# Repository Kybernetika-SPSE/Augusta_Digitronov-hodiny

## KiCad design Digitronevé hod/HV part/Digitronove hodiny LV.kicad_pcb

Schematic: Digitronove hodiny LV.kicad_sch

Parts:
C1, C9: 100 uF; CP_Radial_D6.3mm_P2.50mm
C2, C3, C4, C5, C6, C7: 100 nF; C_1206_3216Metric_Pad1.33x1.80mm_HandSolder
C8: 4.7 µF; CP_Radial_D10.0mm_P5.00mm
H1, H2, H3: MountingHole; MountingHole_2.5mm
J1: Conn_01x02; JST_EH_B2B-EH-A_1x02_P2.50mm_Vertical
J2: Conn_01x09; JST_EH_B9B-EH-A_1x09_P2.50mm_Vertical
NE1, NE2: Lamp_Neon; C_Rect_L4.0mm_W2.5mm_P2.50mm
Q1: MPSA42; TO-92_Inline
R1: 100K; R_Axial_DIN0207_L6.3mm_D2.5mm_P10.16mm_Horizontal
R2, R3, R4, R5: 10k; R_Axial_DIN0207_L6.3mm_D2.5mm_P10.16mm_Horizontal
R6, R7: 180k; R_Axial_DIN0207_L6.3mm_D2.5mm_P10.16mm_Horizontal
R8: 1M; R_Axial_DIN0207_L6.3mm_D2.5mm_P10.16mm_Horizontal
R9: 1k; R_Axial_DIN0207_L6.3mm_D2.5mm_P10.16mm_Horizontal
U1, U2: 74HC595; 74HC595N
U3, U4, U5, U6: K155id1; 74141
U7, U8, U9, U10: Tesla_ZM1082

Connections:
/0a: U6.16 (Q0), U10.11 (k9)
/0b: U5.16 (Q0), U9.11 (k9)
/0c: U4.16 (Q0), U8.11 (k9)
/0d: U3.16 (Q0), U7.11 (k9)
/1a: U6.15 (Q1), U10.9 (k8)
/1b: U5.15 (Q1), U9.9 (k8)
/1c: U4.15 (Q1), U8.9 (k8)
/1d: U3.15 (Q1), U7.9 (k8)
/2a: U6.8 (Q2), U10.8 (k7)
/2b: U5.8 (Q2), U9.8 (k7)
/2c: U4.8 (Q2), U8.8 (k7)
/2d: U3.8 (Q2), U7.8 (k7)
/3a: U6.9 (Q3), U10.7 (k6)
/3b: U5.9 (Q3), U9.7 (k6)
/3c: U4.9 (Q3), U8.7 (k6)
/3d: U3.9 (Q3), U7.7 (k6)
/4a: U6.13 (Q4), U10.6 (k5)
/4b: U5.13 (Q4), U9.6 (k5)
/4c: U4.13 (Q4), U8.6 (k5)
/4d: U3.13 (Q4), U7.6 (k5)
/5a: U6.14 (Q5), U10.5 (k4)
/5b: U5.14 (Q5), U9.5 (k4)
/5c: U4.14 (Q5), U8.5 (k4)
/5d: U3.14 (Q5), U7.5 (k4)
/6a: U6.11 (Q6), U10.3 (k3)
/6b: U5.11 (Q6), U9.3 (k3)
/6c: U4.11 (Q6), U8.3 (k3)
/6d: U3.11 (Q6), U7.3 (k3)
/7a: U6.10 (Q7), U10.2 (k2)
/7b: U5.10 (Q7), U9.2 (k2)
/7c: U4.10 (Q7), U8.2 (k2)
/7d: U3.10 (Q7), U7.2 (k2)
/8a: U6.1 (Q8), U10.1 (k1)
/8b: U5.1 (Q8), U9.1 (k1)
/8c: U4.1 (Q8), U8.1 (k1)
/8d: U3.1 (Q8), U7.1 (k1)
/9a: U6.2 (Q9), U10.12 (k0)
/9b: U5.2 (Q9), U9.12 (k0)
/9c: U4.2 (Q9), U8.12 (k0)
/9d: U3.2 (Q9), U7.12 (k0)
/+3V3: C1.1, C1.2, C2.2, C3.2, J2.3, U1.10 (~SRCLR), U1.16 (VCC), U2.10 (~SRCLR), U2.16 (VCC)
/+170V: C8.1, J1.2, NE1.1, NE1.2, NE2.1, NE2.2, Q1.1 (E), R2.1, R2.2, R3.1, R3.2, R4.1, R4.2, R5.1, R5.2, R6.1, R6.2, R7.1, R7.2, R8.2, R9.1, R9.2, U7.13 (a), U8.13 (a), U9.13 (a), U10.13 (a)
/A1: U2.15 (QA), U6.3 (A)
/A2: U2.4 (QE), U5.3 (A)
/A3: U1.15 (QA), U4.3 (A)
/A4: U1.4 (QE), U3.3 (A)
/B1: U2.1 (QB), U6.6 (B)
/B2: U2.5 (QF), U5.6 (B)
/B3: U1.1 (QB), U4.6 (B)
/B4: U1.5 (QF), U3.6 (B)
/C1: U2.2 (QC), U6.7 (C)
/C2: U2.6 (QG), U5.7 (C)
/C3: U1.2 (QC), U4.7 (C)
/C4: U1.6 (QG), U3.7 (C)
/D1: U2.3 (QD), U6.4 (D)
/D2: U2.7 (QH), U5.4 (D)
/D3: U1.3 (QD), U4.4 (D)
/D4: U1.7 (QH), U3.4 (D)
/NE1,2: J2.1, Q1.2 (B), R1.1
/OE: J2.8, U1.13 (~OE), U2.13 (~OE)
/RLCK: J2.7, U1.12 (RCLK), U2.12 (RCLK)
/SER1: J2.9, U2.14 (SER)
/SER2: U1.14 (SER), U2.9 (QH')
/SRLCK: J2.6, U1.11 (SRCLK), U2.11 (SRCLK)
GND: C2.1, C3.1, C4.2, C5.2, C6.2, C7.2, C8.2, J1.1, J2.4, J2.5, Q1.3 (C), R1.2, R8.1, U1.8 (GND), U2.8 (GND), U3.12 (GND), U4.12 (GND), U5.12 (GND), U6.12 (GND)

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
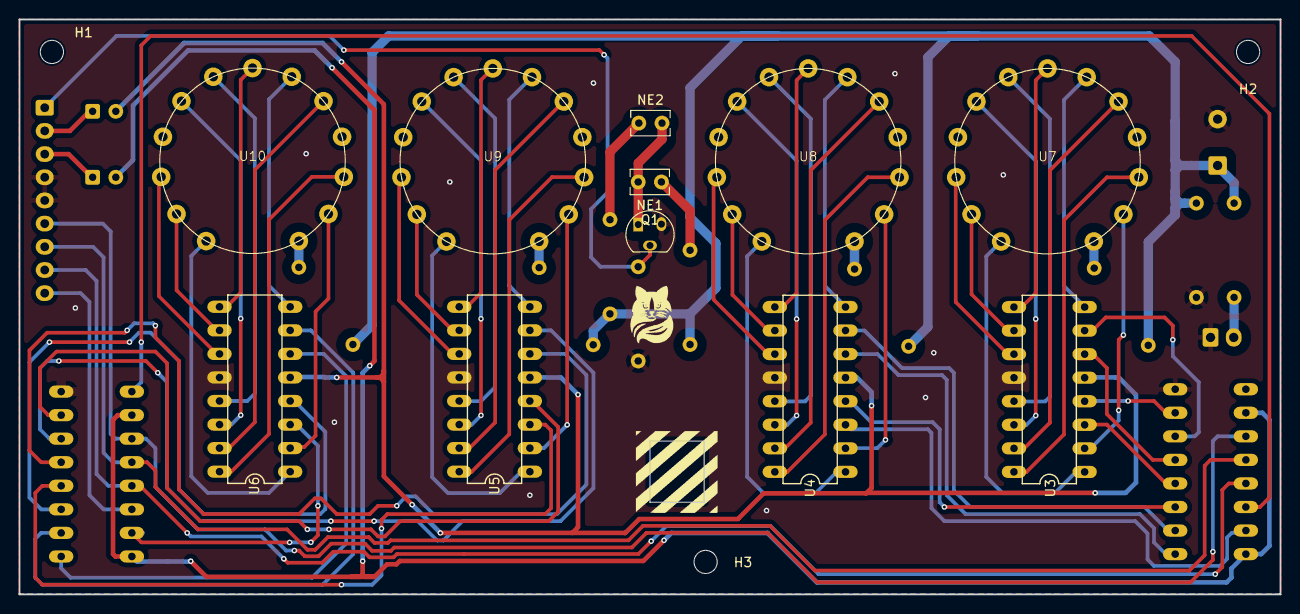
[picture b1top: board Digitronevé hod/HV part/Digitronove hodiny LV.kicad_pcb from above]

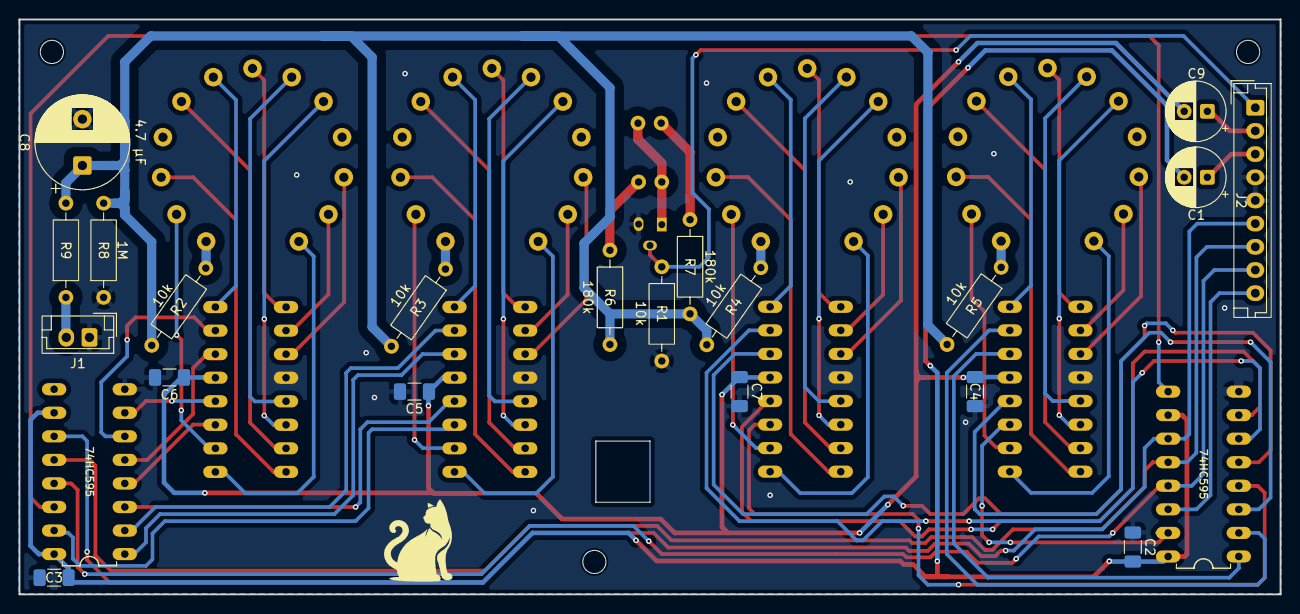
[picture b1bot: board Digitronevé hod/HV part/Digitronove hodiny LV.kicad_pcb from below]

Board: 2 copper layers, 136.0 x 62.0 mm, 36 parts (22 on the bottom side), 66 nets.

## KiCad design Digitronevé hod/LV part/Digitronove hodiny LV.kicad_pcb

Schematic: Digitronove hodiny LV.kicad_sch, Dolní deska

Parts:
C1: 100uF; CP_Radial_D6.3mm_P2.50mm
C2, C3, C4: 100nF; C_1206_3216Metric_Pad1.33x1.80mm_HandSolder
D1: 1N5817; D_DO-41_SOD81_P10.16mm_Horizontal
DS1: Conn_01x06; DS3231
F1, F2: Fuse; Fuse_1812_4532Metric
H1, H2, H3: MountingHole; MountingHole_2.5mm
J1: PDC004-PD
J2: MAX1771
J4: GY-VL53L0X
Konektor1: Conn_01x09; JST_EH_B9B-EH-A_1x09_P2.50mm_Vertical
Q1: NPN
R1, R3: 10k; R_1206_3216Metric_Pad1.30x1.75mm_HandSolder
R2, R4, R5, R6, R7, R8, R9, R10, R11: 4.7k; R_1206_3216Metric_Pad1.30x1.75mm_HandSolder
SW1: START/STOP; SW_PUSH_6mm_H4.3mm
SW2: EN; SW_PUSH_6mm_H4.3mm
SW3: +1; SW_PUSH_6mm_H4.3mm
SW4: SWITCH; SW_PUSH_6mm_H4.3mm
U1: DD4012SA; Untitled_3
U2: ESP32 DevKit; MODULE_ESP32_DEVKIT_V1; PARTREV N/A

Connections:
/+1: C3.2, R10.2, U2.21 (D32)
/+3V3: DS1.+3V3, J4.+3V3, Konektor1.3, R1.1, R2.1, R4.2, R6.1, R6.2, R7.1, R8.1, R8.2, R9.1, R9.2, R10.1, R11.1, SW1.2, SW3.2, SW4.2, U2.1 (3V3)
/+5V: C1.1, D1.1 (K), D1.2 (A), Konektor1.2, U1.3 (OUT), U2.30 (VIN)
/+9V: F1.1, F1.2, F2.1, F2.2, J1.1, J2.VIN (Pin_1), U1.1 (IN)
/EN: SW2.2, U2.16 (EN)
/NE1,2: Konektor1.1, R5.1, R5.2, U2.4 (D2)
/OE: Konektor1.8, U2.14 (D22)
/RLCK: Konektor1.7, U2.23 (D25)
/SCL: DS1.SCL, J4.SCL, R2.2, U2.5 (D4)
/SDA: DS1.SDA, J4.SDA, R4.1, U2.9 (D18)
/SER1: Konektor1.9, U2.25 (D27)
/SHDN: J2.SHDN (Pin_3), Q1.1 (C), Q1.2 (B), R3.1, R3.2, U2.28 (D13)
/SQW: DS1.SQW, R1.2, U2.20 (D35)
/SRLCK: Konektor1.6, U2.24 (D26)
/START-STOP: C2.2, R7.2, U2.15 (D23)
/SWITCH: C4.2, R11.2, U2.22 (D33)
GND: C1.2, C2.1, C3.1, C4.1, DS1.GND, J1.2, J2.GND (Pin_2), J4.GND, Konektor1.4, Konektor1.5, Q1.3 (E), SW1.1, SW2.1, SW3.1, SW4.1, U1.2 (GND), U2.2 (GND), U2.29 (GND)

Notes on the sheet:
USB-C s modulem Ip2721

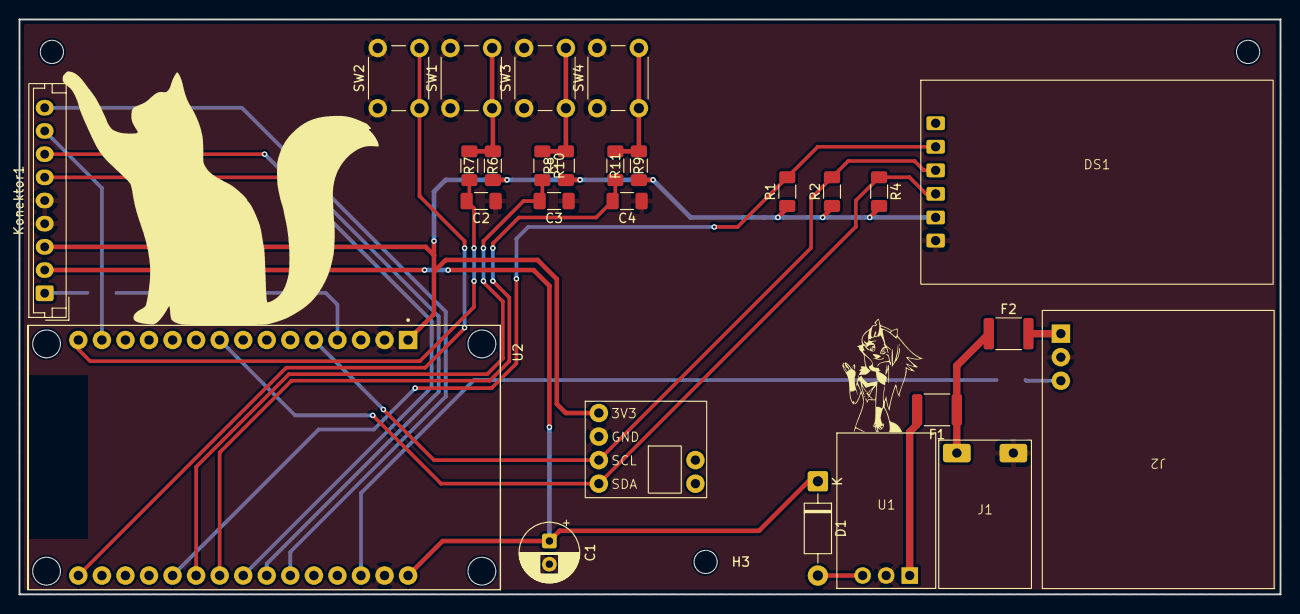
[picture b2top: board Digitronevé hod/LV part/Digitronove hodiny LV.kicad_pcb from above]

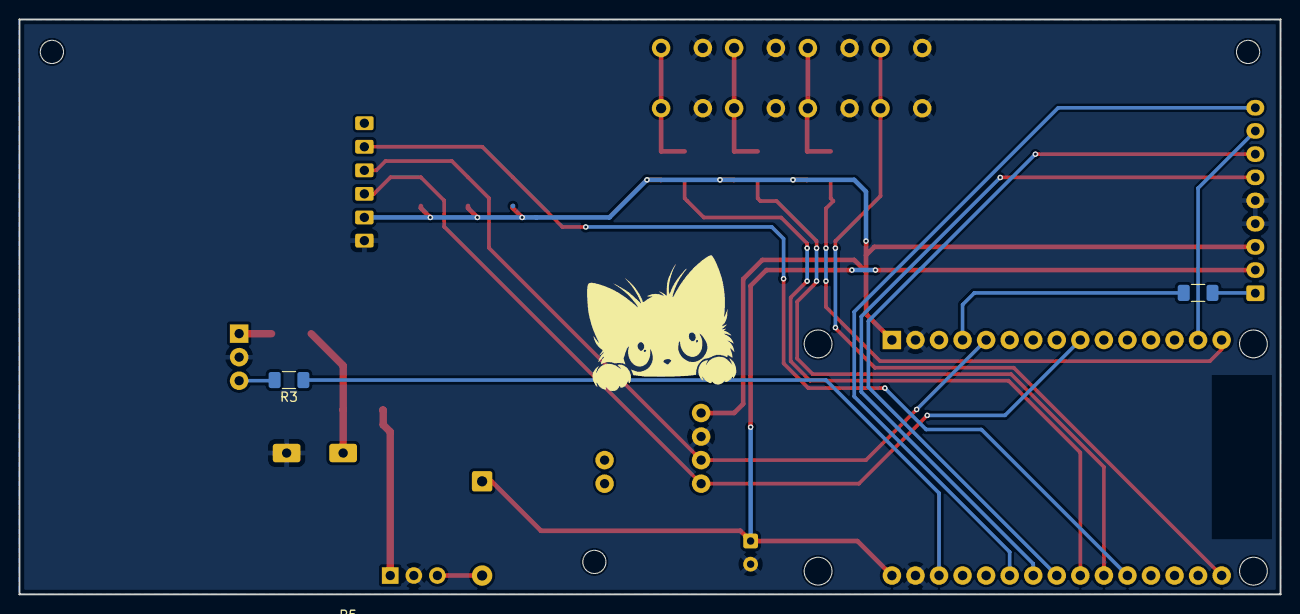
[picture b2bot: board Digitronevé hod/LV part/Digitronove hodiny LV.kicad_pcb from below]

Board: 2 copper layers, 136.0 x 62.0 mm, 32 parts (2 on the bottom side), 17 nets.

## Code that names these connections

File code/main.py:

from machine import Pin, I2C
import time


led = Pin(2, Pin.OUT)


for i in range(1):
    led.value(1)       
    time.sleep(0.2)    
    led.value(0)       
    time.sleep(0.2)    

try:
    import ds3231
    import vl53l0x
    i2c_available = True
except ImportError:
    i2c_available = False

# --- NASTAVENI PINU PODLE SCHEMATU ---
btn_start_stop = Pin(23, Pin.IN) 
btn_plus_one   = Pin(32, Pin.IN) 
btn_switch     = Pin(33, Pin.IN) 

# Posuvne registry 74HC595
pin_ser   = Pin(27, Pin.OUT) 
pin_srclk = Pin(26, Pin.OUT) 
pin_rlck  = Pin(25, Pin.OUT) 
pin_oe    = Pin(22, Pin.OUT)  

# Bezpecne vychozi stavy pro 74HC595 (zadne nahodne pulzy pri startu)
pin_ser.value(0)
pin_srclk.value(0)
pin_rlck.value(0)
pin_oe.value(0)

# NOVE PINY: Menic a Tecky
pin_shdn  = Pin(13, Pin.OUT) # SHDN - Zapinani 170V menice (IO14)
pin_dots  = Pin(2, Pin.OUT)  # D2 - Zapinani tecek mezi cislicemi (GPIO 2)

# --- INICIALIZACE I2C a SENZORU ---
i2c = I2C(0, scl=Pin(4), sda=Pin(18), freq=400000)

if i2c_available:
    rtc = ds3231.DS3231(i2c)
    sensor = vl53l0x.VL53L0X(i2c) # Tady ho rovnou pojmenujeme sensor

# --- GLORBO FLORBO
current_hour = 00
current_minute = 00
display_on = False
frozen_time = False
freeze_start_time = 0
set_mode = 0 # 0 = Bezny provoz, 1 = Nastaveni HODIN, 2 = Nastaveni MINUT
posledni_pohyb_cas = time.ticks_ms() 

# --- Fce ---
def turn_on_display():
    global display_on
    pin_oe.value(0)   
    pin_shdn.value(1) 
    display_on = True

def turn_off_display():
    global display_on
    pin_shdn.value(0) 
    pin_oe.value(1)  
    pin_dots.value(0) 
    display_on = False

def dec_to_bcd(val):
    """Prevede klasicke cislo (napr. 34) na BCD format pro K155ID1"""
    tens = val // 10
    units = val % 10
    return (tens << 4) | units

def update_shift_registers(hours, minutes):
    bcd_hours = dec_to_bcd(hours)
    bcd_minutes = dec_to_bcd(minutes)
    
    # hod:min
    data_to_send = (bcd_hours << 8) | bcd_minutes

    # Pri shiftovani docasne vypneme vystup, aby nevznikaly artefakty.
    output_was_enabled = (pin_oe.value() == 0)
    if output_was_enabled:
        pin_oe.value(1)
    
    pin_rlck.value(0)
    for i in range(15, -1, -1):
        bit = (data_to_send >> i) & 1
        pin_ser.value(bit)

        pin_srclk.value(1)
        pin_srclk.value(0)
        
    pin_rlck.value(1)
    pin_rlck.value(0)

    if output_was_enabled:
        pin_oe.value(0)
    
    

    # --- HLAVNI SMYCAK  ---
while True:
    now = time.ticks_ms()
    
    if i2c_available:
        try:
            distance = sensor.read() 
            if distance >= 150 and distance <= 300:
                posledni_pohyb_cas = now 
                if not display_on:
                    turn_on_display()
        except:
            pass 
            
    # === CTENI REALNEHO CASU Z RTC ===
    if i2c_available and set_mode == 0 and not frozen_time:
        try:
            cas = rtc.datetime() 
        
            current_hour = cas[4]   
            current_minute = cas[5] 
        except:
            pass
            
    # 2. ZHASINANI DIGITRONEK
    if display_on and set_mode == 0:
        if time.ticks_diff(now, posledni_pohyb_cas) > 8000:
            turn_off_display()

    # 3. DOTS
    if display_on:
        if set_mode == 0:
            if (now % 2000) < 1000:
                pin_dots.value(1)
            else:
                pin_dots.value(0)
        else:
            pin_dots.value(1)
    
    # 4. Zmrazeni casu 
    if btn_start_stop.value() == 0:
        if not frozen_time:
            frozen_time = True
            freeze_start_time = now
        time.sleep(0.3)
            
    if frozen_time and time.ticks_diff(now, freeze_start_time) > 10000:
        frozen_time = False

    # 5. Prepinani rezimu nastaveni (Switch) a ULOZENI CASU
    if btn_switch.value() == 0:
        stary_rezim = set_mode
        set_mode = (set_mode + 1) % 3
        

        if stary_rezim != 0 and set_mode == 0 and i2c_available:
            try:
                novy_cas = (2025, 1, 1, current_hour, current_minute, 0, 0)
                rtc.datetime(novy_cas)
                
            except:
                pass

        posledni_pohyb_cas = now
        if not display_on: turn_on_display()
        time.sleep(0.3)

    # 6. Pridavani casu (+1)
    if btn_plus_one.value() == 0:
        if set_mode == 1:
            current_hour = (current_hour + 1) % 24
        elif set_mode == 2:
            current_minute = (current_minute + 1) % 60
        posledni_pohyb_cas = now 
        if not display_on: turn_on_display()
        time.sleep(0.2) 

    # 7. Zobrazeni 
    if display_on:
        # Pri aktivnim zobrazeni drz drivery trvale zapnute.
        pin_shdn.value(1)
        pin_oe.value(0)
        update_shift_registers(current_hour, current_minute)
    
    time.sleep(0.05)

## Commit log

2025-10-30 Fix project name formatting in README
2025-12-21 PCB 21.12.2025
2025-12-22 Dodání pouzder
2025-12-22 Dodávní pouzder part2
2025-12-22 LV Schema
2025-12-26 schéma LV desky update
2025-12-26 PCB LV upravování pouzder
2025-12-28 Update Schéma LV
2025-12-28 Dokončení LV
2025-12-30 HV part schematic 01
2026-01-03 HV scheme update
2026-01-06 LV update
2026-02-05 Redesign LV
2026-02-16 Před kontrolou
2026-02-21 PCB finnal
2026-03-05 pcb uprava
2026-03-05 uprava
2026-04-09 Final I hope
2026-04-09 release meee
2026-04-09 Final:(
